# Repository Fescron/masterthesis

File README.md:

# Masterthesis

<br/>

<br/>

| Quick access links | |
|------|-----|
| [PCB v1.0 schematic (PDF)](hardware/masterthesis-hardware/Plots/masterthesis-hardware-v1.0.pdf) | [Doxygen code documentation of individual files and methods](https://fescron.github.io/masterthesis/files.html) |
| [PCB v1.0 layout (PDF)](hardware/masterthesis-hardware/Plots/masterthesis-hardware-v1-0-PCB.pdf) | [Doxygen TODO's](https://fescron.github.io/masterthesis/todo.html) |

<br>

This repository is a collection of hardware, firmware and some documentation files for the project I created for my masterthesis.

<br/>

## 0 - Table of Contents

- [Masterthesis](#masterthesis)
  - [0 - Table of Contents](#0---table-of-contents)
  - [1 - Situation](#1---situation)
  - [2 - Hardware](#2---hardware)
  - [3 - Firmware](#3---firmware)
  - [4 - Additional hardware changes (PCB v1.0)](#4---additional-hardware-changes-pcb-v10)

<br/>

## 1 - Situation

The goal of the thesis was to create a module to connect a *Moving Bed BioReactor* (MBBR, schematically pictured below) to the Cloud. A MBBR is a system which removes excess nitrites in, in this case, drainwater coming from greenhouses to prevent eutrophication in surrounding water bodies. This is done by denitrifying bacteria inside the bioreactor, which grow on moving plastic *carriers*, and convert the nitrate to nitrogen gas. This is done in anoxic conditions and in the presence of a suitable electron donor, such as a glycerol-based carbon source.

<br/>

The picture below on the left gives an overview of the system that has already been build on the location. The drainage well from the diagram above is pictured on the lower right of this picture. The MBBR itself and a smaller drainage well are underground, under the two manhole covers on the left. In the middle of the picture the measuring system is visible, with under it two blue barrels of carbon source. The picture below on the right gives a peek inside the MBBR. The plastic *carries* are clearly visible.

<br/>

To get an overview of the added components of the masterthesis (in full-color) in relation to the already existing structures (semi-transparant), a global block diagram (in Dutch) was created which can be seen below.

<br>

The heart of the project is the *EFM32HG222* microcontroller and with a Sparkfun *SerLCD* display it is possible to display status information and measurements. The IoT connection is done with a *BG96* modem over NB-IoT. To get an indication of the amount of water processed by the MBBR, the amount of energy used by the waterpump is monitored with an energy-meter. This gives a pulse to the microcontroller when a certain amount of energy is used. Measurements done by the MBBR system (Hach *sc200*: acidity level, nitrate value, redox value) are acquired via *4-20 mA current loops*. The remaining amount of carbon source in a barrel is measured with a *VL53L1X* sensor. To measure the water temperature a *DS18B20* sensor was chosen, and to get the air temperature (and humidity) a *SHT30* sensor is used.

<br/>

## 2 - Hardware

Below one can see the block diagram of the constructed PCB (inside the big grey rounded rectangle) and the external sensors/modules on the far right. Semi-transparent items are optional for future expansion. The voltages used by the different components are indicated in square brackets. The different interconnecting technologies (I2C, USART, SWD, ADC, GPIO, ...) are indicated inside the MCU block.

<br>

230v mains power is used to power the project. A big SMPS is used to convert this AC voltage to a 3.8v DC voltage, mainly to power the BG96 modem and the display. The logic interfaces of the modem however run on 1.8v (indicated by the rounded brackets), so a level-shifter is used to convert the 3.3v logic signals from the MCU. The 3.8v voltage is then further stepped down to 3.3V using an LDO, for use by the MCU and temperature sensors. A 15V boostconverter is also added to supply power to the energy-meter. The schematic of the project can be found [here](hardware/masterthesis-hardware/Plots/masterthesis-hardware-v1.0.pdf).

<br/>

## 3 - Firmware

To get a better idea of the code functionality a few flowcharts were designed, which can be seen below. The left most diagram indicates the *main code-flow*. The code-flow inside the yellow frames on this main flowchart are elaborated in the two diagrams next to the main diagram. The middle flowchart indicates how different statuses are send to the cloud, and the right one indicates how data is being send to the cloud.

<br>

When starting up the code first initializes all the peripherals (INIT). After this a status message is send (SEND STATUS) indicating that the module started up. It can be noted that there is functionality to make sure the module doesn't *spam* status messages, which can be seen in the middle flowchart. Before sending the status message the display is updated indicating that a status message is being send. After the message has been send to the cloud the display is updated with the latest measurements.

After the startup message has been send new measurements are taken (MEASURE), and subsequently these are send to the cloud (SEND DATA). Prior to sending this data the display is updated with a message that data is being send. Afterwards the new measurements are shown on the display. When all of this is done the internal timer is reset (RESET TIMER) so the module can go back to sleep (SLEEP) and wake up after a predefined amount of time (TIMER END) to take new measurements. The module can also wake up on a button press (BUTTON INT) or on an incoming pulse from the energy meter (PULS INT). If the latter is the case this is directly send to the cloud (SEND DATA).

<br>

## 4 - Additional hardware changes (PCB v1.0)

Even though a lot of time was spend making sure the schematic was correct a bodge had to be made to make sure the modem could be turned correctly on and off with the `PWRKEY` pin. At first this was supposed to be done with the `TXB0108PWR` levelshifter but it turned out this could not work due to the inner workings of this chip. Luckily a lot of testpads and zero-ohm resistors were included in the design and a MOSFET, resistor and bodge-wire could easily be soldered to enable the correct functionality. This can be seen on the first overview picture on this repository.

What can also be seen on this picture is that not all of the components are fitted. Some were not soldered because they were not necessary at that point, like for example the micro-USB port which can be used for firmware updates and configuration of the modem. A 3D-render of the whole project is however given below, only missing the display and surrounding case.

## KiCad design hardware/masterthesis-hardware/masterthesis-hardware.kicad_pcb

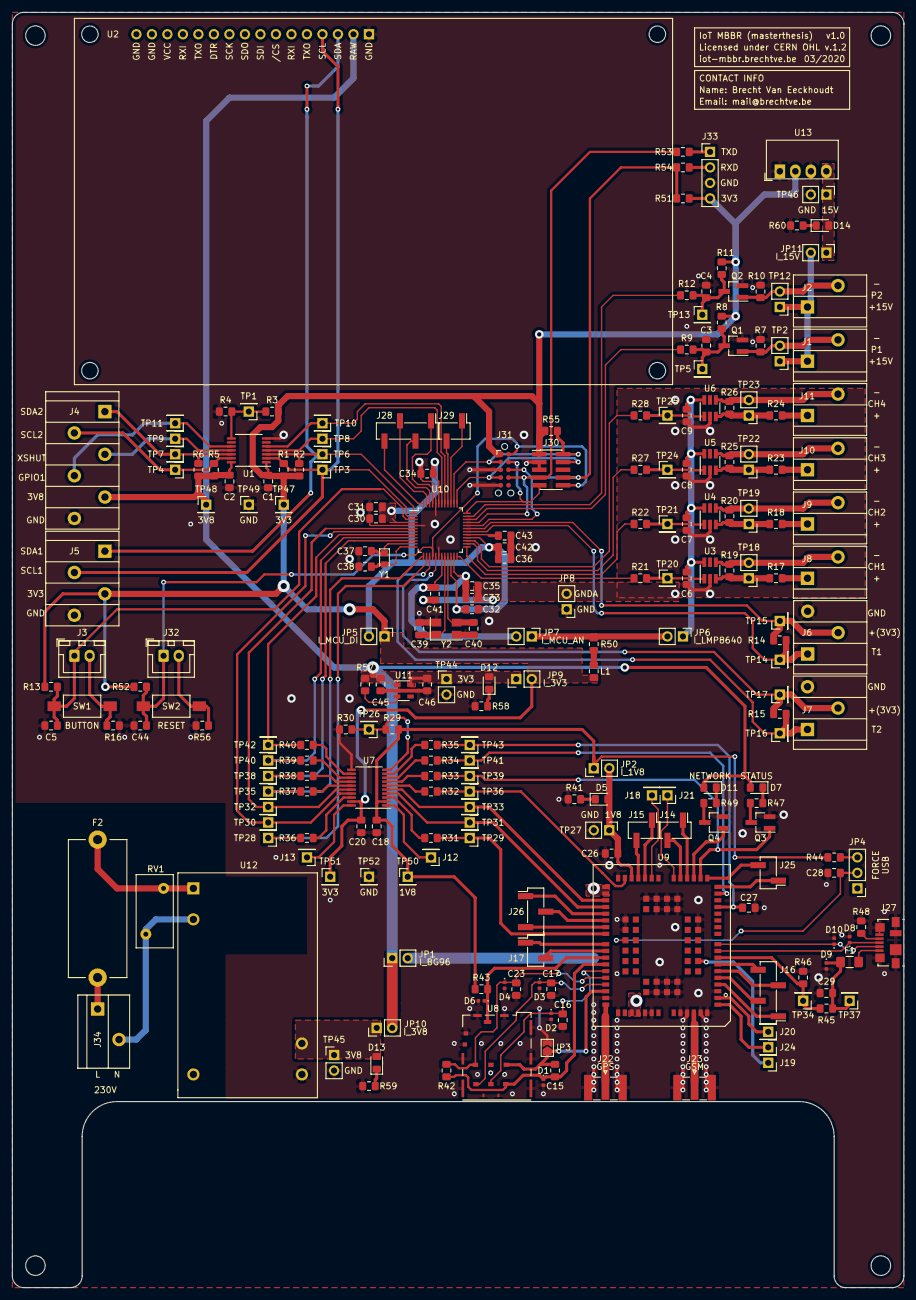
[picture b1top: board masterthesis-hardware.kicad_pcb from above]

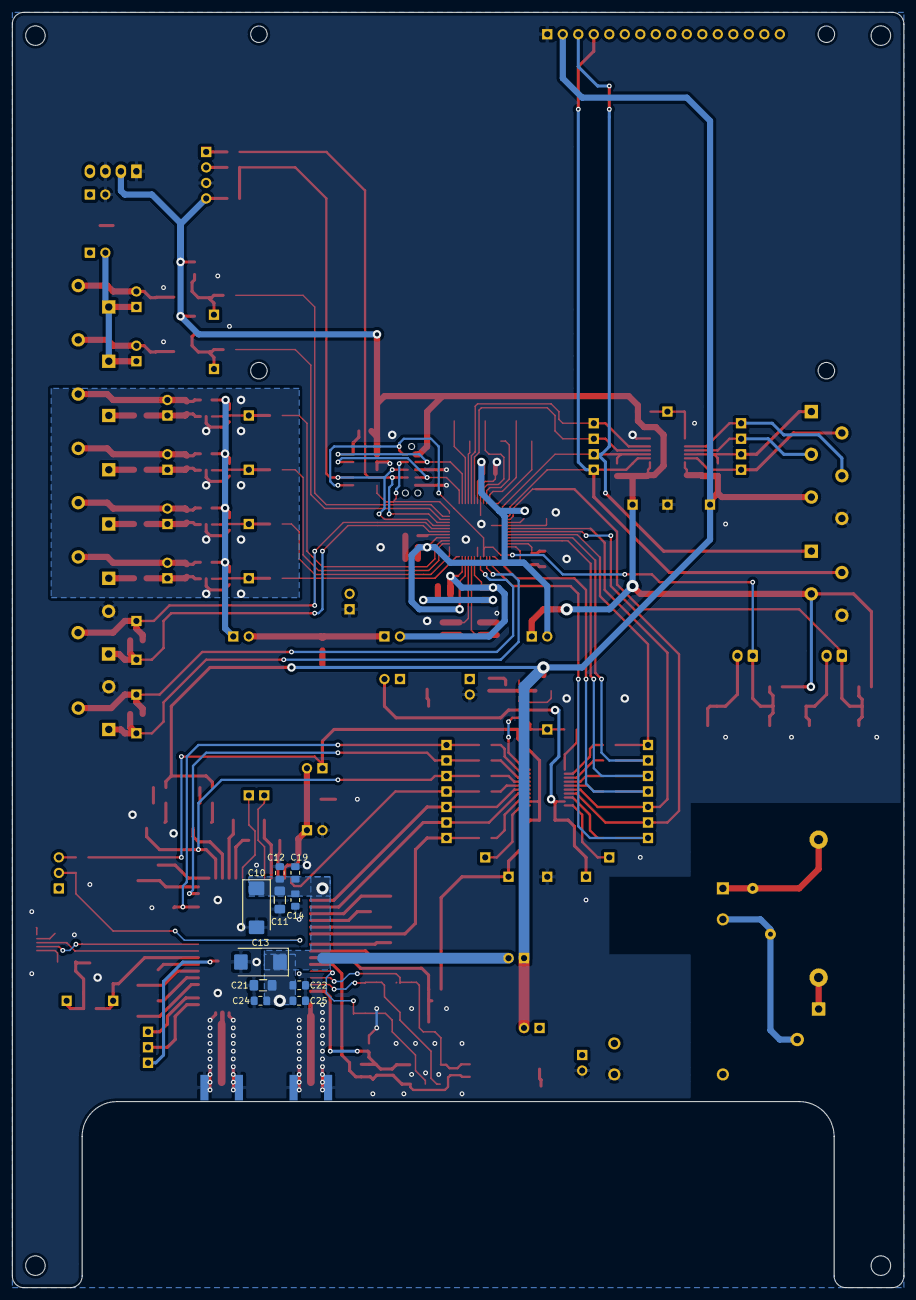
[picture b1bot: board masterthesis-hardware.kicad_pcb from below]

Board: 2 copper layers, 146.1 x 208.9 mm, 247 parts (10 on the bottom side), 153 nets.

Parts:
C1, C2, C3, C4, C6, C7, C8, C9, C12, C15, C18, C20, C22, C29, C31, C32, C34, C42, C44: 100 nF; C_0805_2012Metric_Pad1.15x1.40mm_HandSolder
C5: 1 nF; C_0805_2012Metric_Pad1.15x1.40mm_HandSolder
C10, C13: 470 µF; CP_EIA-7343-43_Kemet-X_Pad2.25x2.55mm_HandSolder
C11, C21: 100 µF; C_1206_3216Metric_Pad1.42x1.75mm_HandSolder
C14, C16, C17, C23, C24: 33 pF; C_0805_2012Metric_Pad1.15x1.40mm_HandSolder
C19, C25: 10 pF; C_0805_2012Metric_Pad1.15x1.40mm_HandSolder
C26: 2,2 µF; C_0805_2012Metric_Pad1.15x1.40mm_HandSolder
C27, C28, C35, C41: 10 nF; C_0805_2012Metric_Pad1.15x1.40mm_HandSolder
C30, C33, C36: 10 µF; C_0805_2012Metric_Pad1.15x1.40mm_HandSolder
C37, C38: 18 pF; C_0805_2012Metric_Pad1.15x1.40mm_HandSolder
C39, C40: 12 pF; C_0805_2012Metric_Pad1.15x1.40mm_HandSolder
C43, C45, C46: 1 µF; C_0805_2012Metric_Pad1.15x1.40mm_HandSolder
D1, D2, D3, D4, D6, D9: SP1003-01ETG; D_0402_1005Metric
D5: RED_1V8; LED_0805_2012Metric_Pad1.15x1.40mm_HandSolder
D7: YELLOW_STATUS; LED_0805_2012Metric_Pad1.15x1.40mm_HandSolder
D8, D10: SP3030-01ETG; D_0402_1005Metric
D11: GREEN_NETWORK; LED_0805_2012Metric_Pad1.15x1.40mm_HandSolder
D12: RED_3V3; LED_0805_2012Metric_Pad1.15x1.40mm_HandSolder
D13: RED_3V8; LED_0805_2012Metric_Pad1.15x1.40mm_HandSolder
D14: RED_15V; LED_0805_2012Metric_Pad1.15x1.40mm_HandSolder
F1: 1206L110SLYR; Fuse_1206_3216Metric_Pad1.42x1.75mm_HandSolder
F2: 32 mA; Fuseholder_Cylinder-5x20mm_Stelvio-Kontek_PTF78_Horizontal_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
G1: Symbol_OSHW-Logo_11.4x12mm; OSHW-Logo_5.7x6mm_SolderMask
H1, H2, H3, H4: MountingHole; MountingHole_3.2mm_M3
J1: PCNT; PhoenixContact_PTSA_1,5_2-G-3,5_1x02_P3.50mm_Angled
J2: PCNT_spare; PhoenixContact_PTSA_1,5_2-G-3,5_1x02_P3.50mm_Angled
J3: PUSH_button; JST_XH_B2B-XH-A_1x02_P2.50mm_Vertical
J4: VL51L1X; PhoenixContact_PTSA_1,5_6-G-3,5_1x06_P3.50mm_Angled
J5: SHT-30; PhoenixContact_PTSA_1,5_4-G-3,5_1x04_P3.50mm_Angled
J6: DS18B20; PhoenixContact_PTSA_1,5_3-G-3,5_1x03_P3.50mm_Angled
J7: DS18B20_spare; PhoenixContact_PTSA_1,5_3-G-3,5_1x03_P3.50mm_Angled
J8, J9, J10, J11: CH4; PhoenixContact_PTSA_1,5_2-G-3,5_1x02_P3.50mm_Angled
J12: A1; PinHeader_1x01_P2.54mm_Vertical
J13: B1; PinHeader_1x01_P2.54mm_Vertical
J14: UART2; PinHeader_1x02_P2.54mm_Vertical_SMD_Pin1Left
J15: UART3; PinHeader_1x02_P2.54mm_Vertical_SMD_Pin1Left
J16: PCM; PinHeader_1x04_P2.54mm_Vertical_SMD_Pin1Left
J17: I2C; PinHeader_1x02_P2.54mm_Vertical_SMD_Pin1Left
J18: GPIO26; PinHeader_1x01_P2.54mm_Vertical
J19: GPIO64; PinHeader_1x01_P2.54mm_Vertical
J20: ADC1; PinHeader_1x01_P2.54mm_Vertical
J21: ADC0; PinHeader_1x01_P2.54mm_Vertical
J22, J23: SMA-edge; SMA_Samtec_SMA-J-P-X-ST-EM1_EdgeMount
J24: PSM_IND; PinHeader_1x01_P2.54mm_Vertical
J25: W/AP; PinHeader_1x02_P2.54mm_Vertical_SMD_Pin1Left
J26: UART1_unused; PinHeader_1x03_P2.54mm_Vertical_SMD_Pin1Left
J27: USB_B_Micro; USB_Micro-B_Molex_47346-0001
J28: GPIO_PE_spare; PinHeader_1x04_P2.54mm_Vertical_SMD_Pin1Left
J29: GPIO_PF_spare; PinHeader_1x02_P2.54mm_Vertical_SMD_Pin1Left
J30: DebugHeader_Cortex-M_SWD_UART_10p; PinHeader_2x05_P1.27mm_Vertical_SMD
J31: DebugHeader_Cortex-M_JTAG_10p_TagConnect; Tag-Connect_TC2050-IDC-NL_2x05_P1.27mm_Vertical
J32: RESET_button; JST_XH_B2B-XH-A_1x02_P2.50mm_Vertical
J33: DebugHeader_UART_4p; PinHeader_1x04_P2.54mm_Vertical
J34: 230V input; PhoenixContact_PTSA_1,5_2-G-3,5_1x02_P3.50mm_Angled
JP1: I_BG96; PinHeader_1x02_P2.54mm_Vertical
JP2: I_1V8; PinHeader_1x02_P2.54mm_Vertical
JP3: GND_USIM_GND; SolderJumper-2_P1.3mm_Open_TrianglePad1.0x1.5mm
JP4: USB_BOOT; PinHeader_1x03_P2.54mm_Vertical
JP5: I_MCU_DI; PinHeader_1x02_P2.54mm_Vertical
JP6: I_LPM8640; PinHeader_1x02_P2.54mm_Vertical
JP7: I_MCU_AN; PinHeader_1x02_P2.54mm_Vertical
JP8: GND_GNDA; PinHeader_1x02_P2.54mm_Vertical
JP9: I_3V3; PinHeader_1x02_P2.54mm_Vertical
JP10: I_3V8; PinHeader_1x02_P2.54mm_Vertical
JP11: I_15V; PinHeader_1x02_P2.54mm_Vertical
L1: BLM21BD102SN1D; L_0805_2012Metric_Pad1.15x1.40mm_HandSolder
Q1, Q2: 2N7002-7-F; SOT-23_Handsoldering
Q3, Q4: MMUN2233LT1G; SOT-23_Handsoldering
R1, R2, R3, R5, R6, R7, R8, R10, R11, R14, R15, R29, R44, R51, R57, R60: 10 kΩ; R_0805_2012Metric_Pad1.15x1.40mm_HandSolder
R4, R30: 120 kΩ; R_0805_2012Metric_Pad1.15x1.40mm_HandSolder
R9, R12, R17, R18, R21, R22, R23, R24, R27, R28, R31, R32, R33, R34, R35, R36, R37, R38, R39, R40: 0 Ω; R_0805_2012Metric_Pad1.15x1.40mm_HandSolder
R13, R48: 1 MΩ; R_0805_2012Metric_Pad1.15x1.40mm_HandSolder
R16, R41, R53, R54, R56: 100 Ω; R_0805_2012Metric_Pad1.15x1.40mm_HandSolder
R19, R20, R25, R26: 6,2 Ω; R_0805_2012Metric_Pad1.15x1.40mm_HandSolder
R42: 15 kΩ; R_0805_2012Metric_Pad1.15x1.40mm_HandSolder
R43: 51 kΩ; R_0805_2012Metric_Pad1.15x1.40mm_HandSolder
R45, R52, R58: 1 kΩ; R_0805_2012Metric_Pad1.15x1.40mm_HandSolder
R46: 2.2 kΩ; R_0805_2012Metric_Pad1.15x1.40mm_HandSolder
R47, R49: 2,2 kΩ; R_0805_2012Metric_Pad1.15x1.40mm_HandSolder
R50: 1 Ω; R_0805_2012Metric_Pad1.15x1.40mm_HandSolder
R55: 100 kΩ; R_0805_2012Metric_Pad1.15x1.40mm_HandSolder
R59: 1, 47 kΩ; R_0805_2012Metric_Pad1.15x1.40mm_HandSolder
RV1: ERZ-E08A391CS; RV_Disc_D12mm_W6.1mm_P7.5mm
SW1, SW2: SW_Push; SW_SPST_FSMSM
TP1: TXS0104_OE; PinHeader_1x01_P2.54mm_Vertical
TP2: PCNT; PinHeader_1x02_P2.54mm_Vertical
TP3: SCL_3V3; PinHeader_1x01_P2.54mm_Vertical
TP4: SCL_3V8; PinHeader_1x01_P2.54mm_Vertical
TP5: PCNT; PinHeader_1x01_P2.54mm_Vertical
TP6: SDA_3V3; PinHeader_1x01_P2.54mm_Vertical
TP7: SDA_3V8; PinHeader_1x01_P2.54mm_Vertical
TP8: XSHUT_3V3; PinHeader_1x01_P2.54mm_Vertical
TP9: XSHUT_3V8; PinHeader_1x01_P2.54mm_Vertical
TP10: GPIO1_3V3; PinHeader_1x01_P2.54mm_Vertical
TP11: GPIO1_3V8; PinHeader_1x01_P2.54mm_Vertical
TP12: PCNT_spare; PinHeader_1x02_P2.54mm_Vertical
TP13: PCNT_spare; PinHeader_1x01_P2.54mm_Vertical
TP14: DS18B20_DATA; PinHeader_1x01_P2.54mm_Vertical
TP15: DS18B20_VDD; PinHeader_1x01_P2.54mm_Vertical
TP16: DS18B20_DATA_spare; PinHeader_1x01_P2.54mm_Vertical
TP17: DS18B20_VDD_spare; PinHeader_1x01_P2.54mm_Vertical
TP18: CH4; PinHeader_1x02_P2.54mm_Vertical
TP19: CH5; PinHeader_1x02_P2.54mm_Vertical
TP20: ADC_CH4; PinHeader_1x01_P2.54mm_Vertical
TP21: ADC_CH5; PinHeader_1x01_P2.54mm_Vertical
TP22: CH6; PinHeader_1x02_P2.54mm_Vertical
TP23: CH7; PinHeader_1x02_P2.54mm_Vertical
TP24: ADC_CH6; PinHeader_1x01_P2.54mm_Vertical
TP25: ADC_CH7; PinHeader_1x01_P2.54mm_Vertical
TP26: TXS0108_OE; PinHeader_1x01_P2.54mm_Vertical
TP27: +1V8; PinHeader_1x02_P2.54mm_Vertical
TP28: BG96_RI_3V3; PinHeader_1x01_P2.54mm_Vertical
TP29: BG96_RI_1V8; PinHeader_1x01_P2.54mm_Vertical
TP30: BG96_TXD_3V3; PinHeader_1x01_P2.54mm_Vertical
TP31: BG96_TXD_1V8; PinHeader_1x01_P2.54mm_Vertical
TP32: BG96_RXD_3V3; PinHeader_1x01_P2.54mm_Vertical
TP33: BG96_RXD_1V8; PinHeader_1x01_P2.54mm_Vertical
TP34: USB_VBUS; PinHeader_1x01_P2.54mm_Vertical
TP35: BG96_DTR_3V3; PinHeader_1x01_P2.54mm_Vertical
TP36: BG96_DTR_1V8; PinHeader_1x01_P2.54mm_Vertical
TP37: VBUS; PinHeader_1x01_P2.54mm_Vertical
TP38: BG96_STAT_3V3; PinHeader_1x01_P2.54mm_Vertical
TP39: BG96_STAT_1V8; PinHeader_1x01_P2.54mm_Vertical
TP40: BG96_~RESET~_3V3; PinHeader_1x01_P2.54mm_Vertical
TP41: BG96_~RESET~_1V8; PinHeader_1x01_P2.54mm_Vertical
TP42: BG96_PWRKEY_3V3; PinHeader_1x01_P2.54mm_Vertical
TP43: BG96_PWRKEY_1V8; PinHeader_1x01_P2.54mm_Vertical
TP44: +3V3; PinHeader_1x02_P2.54mm_Vertical
TP45: +3V8; PinHeader_1x02_P2.54mm_Vertical
TP46: +15V; PinHeader_1x02_P2.54mm_Vertical
TP47, TP51: 3V3; PinHeader_1x01_P2.54mm_Vertical
TP48: 3V8; PinHeader_1x01_P2.54mm_Vertical
TP49, TP52: GND; PinHeader_1x01_P2.54mm_Vertical
TP50: 1V8; PinHeader_1x01_P2.54mm_Vertical
U1: TXS0104EPWR; TSSOP-14_4.4x5mm_P0.65mm
U2: Sparkfun_20x4_serLCD
U3, U4, U5, U6: LMP8640; SOT-23-6_Handsoldering
U7: TXB0108PWR; TSSOP-20_4.4x6.5mm_P0.65mm
U8: nanoSIM_JAE_SF72S006VBAR2500
U9: Quectel_BG96; Quectel_BG96_LGA102
U10: EFM32HG222; TQFP-48_7x7mm_P0.5mm
U11: TLV75533PDBV; SOT-23-5
U12: RAC03-3.8SC
U13: MEE1S0315SC; Converter_DCDC_Murata_MEE1SxxxxSC_THT
Y1: 32,768 kHz; Crystal_SMD_2012-2Pin_2.0x1.2mm_HandSoldering
Y2: 24 MHz; Crystal_SMD_5032-4Pin_5.0x3.2mm

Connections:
+1V8: C18.1, JP2.1, R29.1, R43.1, R44.1, TP50.1, U7.2
+3V3: C1.1, C20.1, J5.3, J30.1, J31.1, J33.4, JP5.1, JP9.2, L1.1, R1.2, R2.2, R3.1, R8.1, R11.1, R13.2, R51.2, R52.2, R55.2, TP47.1, TP51.1, U1.1, U7.19, U13.2
+3V8: C2.1, C45.1, D7.2, D11.2, J4.5, JP1.1, JP10.2, R5.2, R6.2, R57.1, TP48.1, U1.14, U2.2, U11.1
+15V: J1.1, J2.1, JP11.2, TP2.1, TP12.1
/4x LMP38640/ADC_CH4: R21.2, U10.24
/4x LMP38640/ADC_CH5: R22.2, U10.25
/4x LMP38640/ADC_CH6: R27.2, U10.26
/4x LMP38640/ADC_CH7: R28.2, U10.27
/4x LMP38640/V1+: R17.2, R19.1, TP18.1, U3.3
/4x LMP38640/V1-: J8.2, R19.2, TP18.2, U3.4
/4x LMP38640/V2+: R18.2, R20.1, TP19.1, U4.3
/4x LMP38640/V2-: J9.2, R20.2, TP19.2, U4.4
/4x LMP38640/V3+: R23.2, R25.1, TP22.1, U5.3
/4x LMP38640/V3-: J10.2, R25.2, TP22.2, U5.4
/4x LMP38640/V4+: R24.2, R26.1, TP23.1, U6.3
/4x LMP38640/V4-: J11.2, R26.2, TP23.2, U6.4
/BG96/BG96_DTR: R37.2, TP35.1, U10.13
/BG96/BG96_PWRKEY: R40.2, TP42.1, U10.8
/BG96/BG96_RI: R36.2, TP28.1, U10.14
/BG96/BG96_RXD: TP32.1, U7.16, U10.6
/BG96/BG96_STAT: R38.2, TP38.1, U10.10
/BG96/BG96_TXD: TP30.1, U7.17, U10.7
/BG96/BG96_~RESET: R39.2, TP40.1, U10.9
/BG96/DTR_1V8: R32.1, TP36.1, U9.30
/BG96/NETLIGHT: Q4.1, U9.21
/BG96/PWRKEY: C27.1, R35.1, TP43.1, U9.15
/BG96/RESET_N: R34.1, TP41.1, U9.17
/BG96/RI_1V8: R31.1, TP29.1, U9.39
/BG96/RXD_1V8: TP33.1, U7.5, U9.34
/BG96/STATUS: Q3.1, R33.1, TP39.1, U9.20
/BG96/TXD_1V8: TP31.1, U7.4, U9.35
/BG96/USB_D+: D8.1, J27.3, U9.9
/BG96/USB_D-: D10.1, J27.2, U9.10
/BG96/USB_VBUS: R45.2, R46.1, TP34.1, U9.8
/BG96/USIM_CLK: C17.1, D3.1, U8.C3, U9.46
/BG96/USIM_DATA: C23.1, D4.1, R42.2, U8.C7, U9.45
/BG96/USIM_GND: C15.2, JP3.1, U8.C5, U9.47
/BG96/USIM_PRES: D6.1, R43.2, U8.DSW, U9.42
/BG96/USIM_RST: C16.1, D2.1, U8.C2, U9.44
/BG96/USIM_VDD: C15.1, D1.1, R42.1, U8.C1, U9.43
/BUTTON: C5.1, J3.1, R13.1, SW1.1, U10.3
/DS18B20_DATA: J6.1, R14.2, TP14.1, U10.30
/DS18B20_DATA_spare: J7.1, R15.2, TP16.1, U10.15
/DS18B20_VDD: J6.2, R14.1, TP15.1, U10.31
/DS18B20_VDD_spare: J7.2, R15.1, TP17.1, U10.17
/EFM32HG222/GNDd: J30.9, J31.9, U10.36
/EFM32HG222/HFXTAL_N: C40.1, U10.21, Y2.3
/EFM32HG222/HFXTAL_P: C39.1, U10.20, Y2.1
/EFM32HG222/LFXTAL_N: C38.1, U10.12, Y1.2
/EFM32HG222/LFXTAL_P: C37.1, U10.11, Y1.1
/EFM32HG222/RXD: J30.8, J31.8, R51.1, R54.2, U10.32
/EFM32HG222/SWCLK: J30.4, J31.4, U10.37
/EFM32HG222/SWDIO: J30.2, J31.2, R55.1, U10.38
/EFM32HG222/TXD: J30.7, J31.7, R53.2, U10.33
/EFM32HG222/VDDA_MCU: C33.1, C35.1, C41.1, JP7.2, U10.19, U10.23
/EFM32HG222/VDD_MCU: C30.1, C31.1, C32.1, C34.1, C36.1, C42.1, JP5.2, U10.4, U10.22, U10.28, U10.43
/EFM32HG222/~RESET: C44.1, J30.10, J31.10, J32.1, R52.1, SW2.1, U10.16
/GPIO1_3V3: TP10.1, U1.5, U10.41
/GPIO1_3V8: J4.4, TP11.1, U1.10
/PCNT: R9.1, U10.34
/PCNT_spare: R12.1, U10.35
/SCL_3V3: J5.2, R1.1, TP3.1, U1.2, U2.4, U10.2
/SCL_3V8: J4.2, R5.1, TP4.1, U1.13
/SDA_3V3: J5.1, R2.1, TP6.1, U1.3, U2.3, U10.1
/SDA_3V8: J4.1, R6.1, TP7.1, U1.12
/XSHUT_3V3: TP8.1, U1.4, U10.42
/XSHUT_3V8: J4.3, TP9.1, U1.11
GND: C1.2, C2.2, C3.2, C4.2, C5.2, C10.2, C11.2, C12.2, C13.2, C14.2, C16.2, C17.2, C18.2, C19.2, C20.2, C21.2, C22.2, C23.2, C24.2, C25.2, C26.2, C27.2, C28.2, C29.2, C30.2, C31.2, C32.2, C34.2, C36.2, C37.2, C38.2, C39.2, C40.2, C42.2, C43.2, C44.2, C45.2, C46.2, D1.2, D2.2, D3.2, D4.2, D6.2, D8.2, D9.2, D10.2, J4.6, J5.4, J6.3, J7.3, J22.2, J23.2, J27.5, J27.6, J30.3, J30.5, J31.3, J31.5, J33.3, JP3.2, JP8.1, Q1.2, Q2.2, Q3.2, Q4.2, R4.2, R7.2, R10.2, R16.1, R30.2, R41.2, R46.2, R48.2, R56.1, R58.2, R59.2, R60.2, TP27.2, TP44.2, TP45.2, TP46.2, TP49.1, TP52.1, U1.7, U2.1, U7.11, U8.CSW, U8.GND1, U8.GND2, U8.GND3, U8.GND4, U8.GND5, U8.GND6, U8.GND7, U8.GND8, U8.GND9, U8.GND10, U9.3, U9.31, U9.48, U9.50, U9.54, U9.55, U9.58, U9.59, U9.61, U9.62, U9.67, U9.68, U9.69, U9.70, U9.71, U9.72, U9.73, U9.74, U9.79, U9.80, U9.81, U9.82, U9.89, U9.90, U9.91, U9.100, U9.101, U9.102, U10.5, U10.18, U10.44, U11.2, U12.14, U13.1, U13.3, Y2.2, Y2.4
GNDA: C6.2, C7.2, C8.2, C9.2, C33.2, C35.2, C41.2, JP8.2, U3.2, U4.2, U5.2, U6.2
LINE: F2.1, J34.1
NEUT: J34.2, RV1.2, U12.3
unnamed: C3.1, Q1.3, R8.2, R9.2, TP5.1
unnamed: C4.1, Q2.3, R11.2, R12.2, TP13.1
unnamed: C10.1, C11.1, C12.1, C13.1, C14.1, C19.1, C21.1, C22.1, C24.1, C25.1, JP1.2, U9.32, U9.33, U9.52, U9.53
unnamed: C26.1, D5.2, JP2.2, TP27.1, U9.29
unnamed: C28.1, JP4.2, U9.75
unnamed: C29.1, D9.1, F1.2, R45.1, TP37.1
unnamed: C43.1, U10.29
unnamed: C46.1, D12.2, JP9.1, TP44.1, U11.5
unnamed: D5.1, R41.1
unnamed: D7.1, R47.1
unnamed: D11.1, R49.1
unnamed: D12.1, R58.1
unnamed: D13.1, R59.1
unnamed: D13.2, JP10.1, TP45.1, U12.16
unnamed: D14.1, R60.1
unnamed: D14.2, JP11.1, TP46.1, U13.4
unnamed: F1.1, J27.1
unnamed: F2.2, RV1.1, U12.1
unnamed: J1.2, Q1.1, R7.1, TP2.2
unnamed: J2.2, Q2.1, R10.1, TP12.2
unnamed: J3.2, R16.2, SW1.2
unnamed: J8.1, R17.1
unnamed: J9.1, R18.1
unnamed: J10.1, R23.1
unnamed: J11.1, R24.1
unnamed: J12.1, U7.1
unnamed: J13.1, U7.20
unnamed: J14.1, U9.22
unnamed: J14.2, U9.23
unnamed: J15.1, U9.27
unnamed: J15.2, U9.28
unnamed: J16.1, U9.4
unnamed: J16.2, U9.5
unnamed: J16.3, U9.6
unnamed: J16.4, U9.7
unnamed: J17.1, U9.40
unnamed: J17.2, U9.41
unnamed: J18.1, U9.26
unnamed: J19.1, U9.64
unnamed: J20.1, U9.2
unnamed: J21.1, U9.24
unnamed: J22.1, U9.49
unnamed: J23.1, U9.60
unnamed: J24.1, U9.1
unnamed: J25.1, U9.18
unnamed: J25.2, U9.19
unnamed: J26.1, U9.36
unnamed: J26.2, U9.37
unnamed: J26.3, U9.38
unnamed: J27.4, R48.1
unnamed: J28.1, U10.45
unnamed: J28.2, U10.46
unnamed: J28.3, U10.47
unnamed: J28.4, U10.48
unnamed: J29.1, U10.39
unnamed: J29.2, U10.40
unnamed: J32.2, R56.2, SW2.2
unnamed: J33.1, R53.1
unnamed: J33.2, R54.1
unnamed: JP4.3, R44.2
unnamed: JP6.2, JP7.1, R50.2
unnamed: L1.2, R50.1
unnamed: Q3.3, R47.2
unnamed: Q4.3, R49.2
unnamed: R3.2, R4.1, TP1.1, U1.8
unnamed: R21.1, TP20.1, U3.1
unnamed: R22.1, TP21.1, U4.1
unnamed: R27.1, TP24.1, U5.1
unnamed: R28.1, TP25.1, U6.1
unnamed: R29.2, R30.1, TP26.1, U7.10
unnamed: R31.2, U7.3
unnamed: R32.2, U7.6
unnamed: R33.2, U7.7
unnamed: R34.2, U7.8
unnamed: R35.2, U7.9
unnamed: R36.1, U7.18
unnamed: R37.1, U7.15
unnamed: R38.1, U7.14
unnamed: R39.1, U7.13
unnamed: R40.1, U7.12
unnamed: R57.2, U11.3
VDDA: C6.1, C7.1, C8.1, C9.1, JP6.1, U3.6, U4.6, U5.6, U6.6

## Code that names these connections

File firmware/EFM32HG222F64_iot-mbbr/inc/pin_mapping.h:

/***************************************************************************//**
 * @file pin_mapping.h
 * @brief The pin definitions for the custom board.
 * @version 1.0
 * @author Brecht Van Eeckhoudt
 *
 * ******************************************************************************
 *
 * @section Versions
 *
 *   @li v1.0: Initial version.
 *
 * ******************************************************************************
 *
 * @section License
 *
 *   **Copyright (C) 2020 - Brecht Van Eeckhoudt**
 *
 *   This program is free software: you can redistribute it and/or modify
 *   it under the terms of the **GNU General Public License** as published by
 *   the Free Software Foundation, either **version 3** of the License, or
 *   (at your option) any later version.
 *
 *   This program is distributed in the hope that it will be useful,
 *   but WITHOUT ANY WARRANTY; without even the implied warranty of
 *   MERCHANTABILITY or FITNESS FOR A PARTICULAR PURPOSE.  See the
 *   GNU General Public License for more details.
 *
 *   *A copy of the GNU General Public License can be found in the `LICENSE`
 *   file along with this source code.*
 *
 *   @n
 *
 *   Some methods use code obtained from examples from [Silicon Labs' GitHub](https://github.com/SiliconLabs/peripheral_examples).
 *   These sections are licensed under the Silabs License Agreement. See the file
 *   "Silabs_License_Agreement.txt" for details. Before using this software for
 *   any purpose, you must agree to the terms of that agreement.
 *
 ******************************************************************************/


/* Include guards prevent multiple inclusions of the same header */
#ifndef _PIN_MAPPING_H_
#define _PIN_MAPPING_H_


/* Include necessary for this header file */
#include "em_device.h" /* Include necessary MCU-specific header file */
#include "em_gpio.h"   /* General Purpose IO */


/* I2C */
#define BUS_I2C            	I2C0
#define BUS_I2C_LOC        	I2C_ROUTE_LOCATION_LOC0
#define BUS_SDA_PORT		gpioPortA
#define BUS_SDA_PIN       	0
#define BUS_SCL_PORT      	gpioPortA
#define BUS_SCL_PIN       	1

/* BUTTON */
#define BTN_PORT      		gpioPortA
#define BTN_PIN       		2

/* VL53L1X */
#define VL53L1X_GPIO1_PORT	gpioPortF
#define VL53L1X_GPIO1_PIN	4
#define VL53L1X_XSHUT_PORT	gpioPortF
#define VL53L1X_XSHUT_PIN	5

/* BG96 */
#define BG96_UART           USART1
#define BG96_UART_LOC       0
#define BG96_TXD_PORT       gpioPortC
#define BG96_TXD_PIN        1
#define BG96_RXD_PORT       gpioPortC
#define BG96_RXD_PIN        0
#define BG96_PWRKEY_PORT    gpioPortC
#define BG96_PWRKEY_PIN     2
#define BG96_RESET_PORT     gpioPortC
#define BG96_RESET_PIN      3
#define BG96_STAT_PORT     	gpioPortC
#define BG96_STAT_PIN      	4
#define BG96_DTR_PORT     	gpioPortA
#define BG96_DTR_PIN      	8
#define BG96_RI_PORT     	gpioPortA
#define BG96_RI_PIN      	9

/* DEBUG UART */
#define DBG_UART            USART0
#define DBG_UART_LOC        2
#define DBG_TXD_PORT        gpioPortC
#define DBG_TXD_PIN         11
#define DBG_RXD_PORT        gpioPortC
#define DBG_RXD_PIN         10
#define DBG_GNDD_PORT       gpioPortC
#define DBG_GNDD_PIN        15

/* DS18B20 */
#define TEMP0_DATA_PORT     gpioPortC
#define TEMP0_DATA_PIN      8
#define TEMP0_VDD_PORT      gpioPortC
#define TEMP0_VDD_PIN       9
#define TEMP1_DATA_PORT     gpioPortA
#define TEMP1_DATA_PIN      10
#define TEMP1_VDD_PORT      gpioPortB
#define TEMP1_VDD_PIN       11

/* PULSE INPUTS */
#define PULSE0_PORT         gpioPortC /* PCNT0_S0IN #0 */
#define PULSE0_PIN          13
#define PULSE1_PORT         gpioPortC /* PCNT0_S1IN #0 */
#define PULSE1_PIN          14

/* ADC INPUTS */
#define ADC0_PORT      		gpioPortD /* ADC0_CH4 */
#define ADC0_PIN       		4
#define ADC1_PORT      		gpioPortD /* ADC0_CH5 */
#define ADC1_PIN       		5
#define ADC2_PORT      		gpioPortD /* ADC0_CH6 */
#define ADC2_PIN       		6
#define ADC3_PORT      		gpioPortD /* ADC0_CH7 */
#define ADC3_PIN       		7

/* SPARE */
#define J28_0_PORT			gpioPortE
#define J28_0_PIN			10
#define J28_1_PORT			gpioPortE
#define J28_1_PIN			11
#define J28_2_PORT			gpioPortE
#define J28_2_PIN			12
#define J28_3_PORT			gpioPortE
#define J28_3_PIN			13
#define J29_0_PORT			gpioPortF
#define J29_0_PIN			2
#define J29_1_PORT			gpioPortF
#define J29_1_PIN			3


#endif /* _PIN_MAPPING_H_ */

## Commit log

2020-02-18 Added CERN OHL v1.2. licence
2020-08-31 Added hardware files
2020-08-31 Added firmware files
2020-08-31 Added documentation files
2020-09-01 Fixed documentation and minor debug changes
2020-09-01 Added gitignore
2020-09-01 Added SHT30 functionality
2020-09-01 Fixed DS18B20 timing
2020-09-01 Update gitignore
2020-09-01 Added Doxygen documentation
2020-09-01 Added Doxygen link
2020-09-03 Added ADC CH4/5/6/7 functionality
2020-09-03 Updated documentation
2020-09-03 Updated gitignore
2020-09-03 Added API file
2020-09-03 Updated Doxygen Documentation
2021-09-01 Removed unused file
2021-09-03 Updated input & output path
2021-09-28 Added more documentation

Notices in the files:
hardware/masterthesis-hardware/masterthesis-hardware.kicad_pcb:
Licensed under CERN OHL v.1.2
